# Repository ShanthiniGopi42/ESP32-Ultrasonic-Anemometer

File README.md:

# ESP32-Based Ultrasonic Anemometer

A 2D ultrasonic anemometer designed to measure wind speed and wind direction using ultrasonic transit-time measurements. The project involves electronic circuit design, signal conditioning, microcontroller integration, PCB layout, and Gerber file generation using KiCad.

## Overview

An ultrasonic anemometer measures wind conditions using the propagation time of ultrasonic signals between transducers. Wind affects the travel time of sound along different directions, allowing wind speed and direction to be estimated from the measured transit times.

This project uses an ESP32-S3 microcontroller and four 40 kHz ultrasonic transducers arranged in North, East, South, and West directions. The electronic circuit is designed to support ultrasonic transmission, reception, signal processing, and microcontroller interfacing.

The schematic and PCB layout were developed in KiCad, and Gerber files were generated to prepare the board for fabrication.

## Objectives

- Design an electronic system for measuring wind speed and wind direction using ultrasonic transit-time principles.
- Integrate an ESP32-S3 microcontroller with ultrasonic transmitter and receiver circuits.
- Design the required signal-conditioning and interface circuits.
- Develop the complete circuit schematic using KiCad.
- Create a PCB layout based on the schematic and component footprints.
- Generate Gerber and drill files for PCB manufacturing.
- Prepare the design files and documentation for future hardware fabrication and testing.

## Hardware Components

**Microcontroller:** ESP32-S3 DevKitC-1U for system control and signal processing.

**Ultrasonic Transducers:** Four 40 kHz ultrasonic transducers arranged along the North, East, South, and West directions.

**Signal Conditioning:** Operational amplifier and comparator circuits designed for processing received ultrasonic signals.

**Analog Multiplexing:** Analog multiplexing circuitry for selecting signal paths.

**Power Supply:** Voltage regulation and power-management circuits for the electronic system.

Refer to the project schematic and report for the complete component list and circuit connections.

## Software and Design Tools

**KiCad:** Used for schematic capture, component placement, PCB routing, and manufacturing-file generation.

**Embedded Development:** ESP32-S3-based development for controlling the measurement system. Add the firmware language and development environment here if they are part of your completed work.

## Working Principle

1. Ultrasonic transducers transmit and receive signals across the measurement paths.
2. The transit time of the ultrasonic signals is used to determine the effect of wind on sound propagation.
3. Measurements along different directions can be compared to estimate wind speed and wind direction.
4. The ESP32-S3 is intended to coordinate the measurement process and process the relevant signals.

The accuracy of the measurements depends on the transducer arrangement, timing measurements, signal conditioning, and calibration.

## Circuit and PCB Design

The electronic circuit was developed in KiCad, with separate sections for power regulation, ultrasonic signal transmission and reception, signal conditioning, analog multiplexing, and microcontroller interfacing.

The PCB layout was created from the schematic, with component footprints and routed tracks arranged on the board. Gerber and drill files were then generated for use in PCB fabrication.

## Repository Contents

**`Report/`** – Project report and technical documentation.

**`Kicad Design/`** – KiCad schematic, PCB layout, and associated project files.

**`Gerber Files/`** – PCB manufacturing outputs, including copper layers, solder mask, silkscreen, board outline, and drill files where available.

**`Images/`** – Circuit connection diagrams, PCB layout screenshots, and other project visuals.

## Project Status

Schematic design, PCB layout, and Gerber file generation have been completed. PCB fabrication, hardware integration, and experimental validation remain pending if not yet performed.

## Future Work

- Fabricate the PCB using the generated manufacturing files.
- Assemble and test the circuit with the ESP32-S3 and ultrasonic transducers.
- Develop and validate the firmware for transit-time measurement.
- Calibrate the system and compare its measurements with a reference instrument.
- Evaluate measurement accuracy under different wind conditions.

## Author

**Shanthini G**

Electronics and Communication Engineering

## Project Files

### 1. Firmware
- [ESP32-S3 Arduino Firmware](Ultrasonic_anemometer.ino)

### 2. KiCad Design Files
- [PCB Layout](Kicad%20Design/Kicad%20PCB%20Design/Main.kicad_pcb)
- [Schematic](Kicad%20Design/Kicad%20Schematic/Main.kicad_sch)
- [KiCad Project File](Kicad%20Design/Kicad%20Project/Main.kicad_pro)

### 3. PCB Fabrication Files
- [Gerber Files Folder](Gerber%20Files/)

### 4. Design Images
- [3D PCB Layout](Images/3D%20PCB%20Layout.png)
- [PCB Layout](Images/PCB%20Layout.png)
- [Schematic Layout](Images/Schematic%20Layout.png)
- [Gerber View](Images/Gerber%20View.png)

### 5. Project Report
- [Ultrasonic Anemometer Report](Report/)

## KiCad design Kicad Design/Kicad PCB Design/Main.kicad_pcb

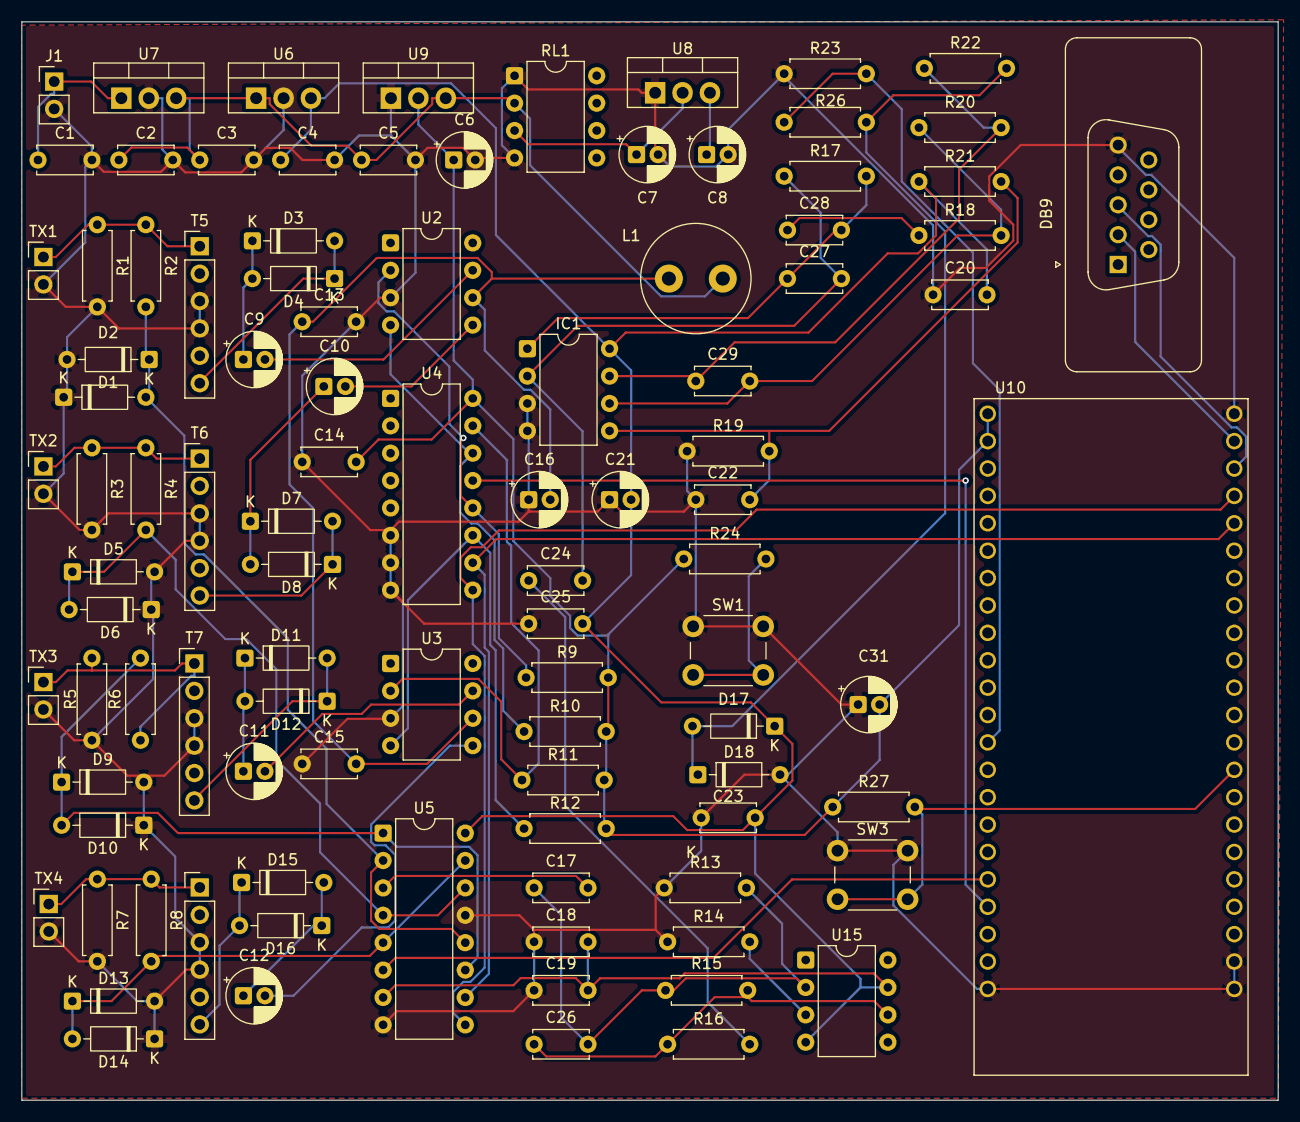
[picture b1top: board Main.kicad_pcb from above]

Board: 2 copper layers, 116.5 x 100.0 mm, 99 parts (0 on the bottom side), 53 nets.

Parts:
C1, C3: 330n; C_Disc_D5.0mm_W2.5mm_P5.00mm
C2, C4, C5, C13, C14, C15, C17, C18, C19, C20, C22, C23, C25: 100n; C_Disc_D5.0mm_W2.5mm_P5.00mm
C6: 10u; CP_Radial_D5.0mm_P2.00mm
C7, C8: 2.2u; CP_Radial_D5.0mm_P2.00mm
C9, C10, C11, C12: 1u; CP_Radial_D5.0mm_P2.00mm
C16: 33u; CP_Radial_D5.0mm_P2.00mm
C21: 4.7u; CP_Radial_D5.0mm_P2.00mm
C24, C28: 10n; C_Disc_D5.0mm_W2.5mm_P5.00mm
C26, C27, C29: 27P; C_Disc_D5.0mm_W2.5mm_P5.00mm
C31: 10uF; CP_Radial_D5.0mm_P2.00mm
D1, D2, D3, D4, D5, D6, D7, D8, D9, D10, D11, D12, D13, D14, D15, D16, D17, D18: 1N4148; D_DO-35_SOD27_P7.62mm_Horizontal
DB9: DB9; DSUB-9_Pins_Vertical_P2.77x2.84mm
IC1: LM833; DIP-8_W7.62mm
J1: Conn_01x02; PinHeader_1x02_P2.54mm_Vertical
L1: L; L_Radial_D10.0mm_P5.00mm_Fastron_07M
R1, R3, R5, R7: 14K; R_Axial_DIN0207_L6.3mm_D2.5mm_P7.62mm_Horizontal
R2, R4, R6, R8, R9, R10, R11, R12, R14, R18, R19, R24, R26, R27: 10K; R_Axial_DIN0207_L6.3mm_D2.5mm_P7.62mm_Horizontal
R13: 100K; R_Axial_DIN0207_L6.3mm_D2.5mm_P7.62mm_Horizontal
R15: 33K; R_Axial_DIN0207_L6.3mm_D2.5mm_P7.62mm_Horizontal
R16: 5.6K; R_Axial_DIN0207_L6.3mm_D2.5mm_P7.62mm_Horizontal
R17: 82K; R_Axial_DIN0207_L6.3mm_D2.5mm_P7.62mm_Horizontal
R20: 68K; R_Axial_DIN0207_L6.3mm_D2.5mm_P7.62mm_Horizontal
R21: R; R_Axial_DIN0207_L6.3mm_D2.5mm_P7.62mm_Horizontal
R22: 330; R_Axial_DIN0207_L6.3mm_D2.5mm_P7.62mm_Horizontal
R23: 20K; R_Axial_DIN0207_L6.3mm_D2.5mm_P7.62mm_Horizontal
RL1: NME1212SC; DIP-8_W7.62mm
SW1, SW3: SW_Push; SW_PUSH_6mm
T5, T6, T7, T8: 78601_1C; PinHeader_1x06_P2.54mm_Vertical
TX1, TX2, TX3, TX4: Speaker_Ultrasound; PinHeader_1x02_P2.54mm_Vertical
U2, U3: ICL7667xPA; DIP-8_W7.62mm
U4, U5: CD4052B; DIP-16_W7.62mm
U6: LM7805_TO220; TO-220-3_Vertical
U7: LM7812_TO220; TO-220-3_Vertical
U8: LM7905_TO220; TO-220-3_Vertical
U9: LD1117V33; TO-220-3_Vertical
U10: ESP32-S3-DEVKITC-1U-N8R8; MODULE_ESP32-S3-DEVKITC-1U-N8R8
U15: OP07; DIP-8_W7.62mm

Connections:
3V3: C6.1, C14.2, C31.2, R9.2, R10.2, R11.2, R12.2, R24.1, R27.1, U4.16 (VDD), U9.2 (VO), U10.J1_1 (3V3), U10.J1_2 (3V3)
+15V: C1.1, J1.1, U7.1 (VI)
/+5V: C4.1, C18.2, C19.2, C20.2, C21.2, C23.2, C25.2, D17.1 (K), IC1.8, R21.1, U5.7 (VEE), U5.16 (VDD), U6.3 (VO), U15.4 (V-), U15.7 (V+)
/+12V: C2.1, C3.1, C5.1, L1.2, RL1.2 (+VIN), U6.1 (VI), U7.3 (VO), U9.3 (VI)
/-5V: C8.1, U8.3 (VO)
/A: U4.10 (A), U5.10 (A), U10.J3_5 (GPIO2)
/B: U4.9 (B), U5.9 (B), U10.J3_4 (GPIO1)
/CHIP PU: R24.2, SW1.2
/GPIO3: R23.2, R26.1, U10.J1_13 (GPIO3)
/GPIO12: U5.6 (INH), U10.J1_18 (GPIO12)
/GPIO13: U4.13 (X), U10.J1_19 (GPIO13)
/Sensor out: C17.1, C26.2, R13.2, R15.1, U15.2 (-)
/U0RXD: DB9.3, U10.J3_3 (U0RXD/GPIO44)
/U0TXD: DB9.2, U10.J3_2 (U0TXD/GPIO43)
GND: C1.2, C2.2, C3.2, C4.2, C5.2, C6.2, C7.2, C8.2, C13.2, C14.1, C15.1, C16.1, C18.1, C19.1, C20.1, C21.1, C22.1, C23.1, C25.1, C31.1, D1.2 (A), D2.1 (K), D5.2 (A), D6.1 (K), D9.2 (A), D10.1 (K), D13.2 (A), D14.1 (K), D18.2 (A), DB9.5, IC1.3, IC1.4, J1.2, R1.2, R3.2, R5.2, R7.2, R13.1, R14.1, R19.1, R23.1, RL1.1 (-VIN), RL1.4 (+VOUT), SW1.1, SW3.1, T5.3 (PRI_2), T5.4 (SEC_1), T6.3 (PRI_2), T6.4 (SEC_1), T7.3 (PRI_2), T7.4 (SEC_1), T8.3 (PRI_2), T8.4 (SEC_1), TX1.2, TX2.2, TX3.2, TX4.2, U2.3 (V-), U3.3 (V-), U4.6 (INH), U4.7 (VEE), U4.8 (VSS), U5.8 (VSS), U5.13 (X), U6.2 (GND), U7.2 (GND), U8.1 (GND), U9.1 (GND), U10.J1_22 (GND), U10.J3_1 (GND), U10.J3_21 (GND), U10.J3_22 (GND)
unnamed: C22.2, IC1.5, R19.2, R21.2
unnamed: C24.1, R16.2
unnamed: C24.2, C27.2, IC1.2, R17.1
unnamed: C26.1, R15.2, R16.1, U15.6
unnamed: C27.1, C28.2, IC1.1, R17.2
unnamed: C28.1, R18.1
unnamed: C29.1, IC1.7, R20.2, R22.1
unnamed: C29.2, IC1.6, R18.2, R20.1
unnamed: D1.1 (K), D2.2 (A), R2.2, U5.2 (Y2), U5.12 (X0)
unnamed: D3.2 (A), D4.1 (K), T5.6 (SEC_2)
unnamed: C9.1, D3.1 (K), D4.2 (A)
unnamed: D5.1 (K), D6.2 (A), R4.2, U5.4 (Y3), U5.14 (X1)
unnamed: D7.2 (A), D8.1 (K), T6.6 (SEC_2)
unnamed: C10.1, D7.1 (K), D8.2 (A)
unnamed: D9.1 (K), D10.2 (A), R6.2, U5.1 (Y0), U5.11 (X3)
unnamed: D11.2 (A), D12.1 (K), T7.6 (SEC_2)
unnamed: C11.1, D11.1 (K), D12.2 (A)
unnamed: D13.1 (K), D14.2 (A), R8.2, U5.5 (Y1), U5.15 (X2)
unnamed: C12.1, D15.2 (A), D16.1 (K)
unnamed: D15.1 (K), D16.2 (A), T8.6 (SEC_2)
unnamed: D17.2 (A), D18.1 (K), R22.2, R26.2
unnamed: C7.1, RL1.3 (-VOUT), U8.2 (VI)
unnamed: R1.1, R2.1, T5.1 (PRI_1), TX1.1
unnamed: R3.1, R4.1, T6.1 (PRI_1), TX2.1
unnamed: R5.1, R6.1, T7.1 (PRI_1), TX3.1
unnamed: R7.1, R8.1, T8.1 (PRI_1), TX4.1
unnamed: R9.1, U2.2 (IN_A), U4.12 (X0)
unnamed: R10.1, U2.4 (IN_B), U4.14 (X1)
unnamed: C13.1, C15.2, C16.2, L1.1, U2.6 (V+), U3.6 (V+)
unnamed: C9.2, U2.7 (~OUT_A)
unnamed: C10.2, U2.5 (~OUT_B)
unnamed: R11.1, U3.2 (IN_A), U4.15 (X2)
unnamed: R12.1, U3.4 (IN_B), U4.11 (X3)
unnamed: C11.2, U3.7 (~OUT_A)
unnamed: C12.2, U3.5 (~OUT_B)
unnamed: C17.2, U5.3 (Y)
unnamed: R27.2, SW3.2, U10.J3_14 (GPIO0)
unnamed: R14.2, U15.3 (+)
